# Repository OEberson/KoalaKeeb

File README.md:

# KoalaKeeb

In this repo, I am sharing with you my ideal split keyboard, The KoalaKeeb. It is heavily inspired by the [Ferris Sweep](https://github.com/davidphilipbarr/Sweep) and borrows its physical layout. What it adds is ten SK6812 MINI-E LEDs next to the MCU that will be used to display the current battery status or bluetooth profile and a cute koala logo. I will implement the LED functionality in [my ZMK fork](https://github.com/OEberson/zmkoala) soon.

Note that the current PCB version has some imperfections that I will improve on in a second revision.

[Link to my layout](https://github.com/OEberson/zmk-config)

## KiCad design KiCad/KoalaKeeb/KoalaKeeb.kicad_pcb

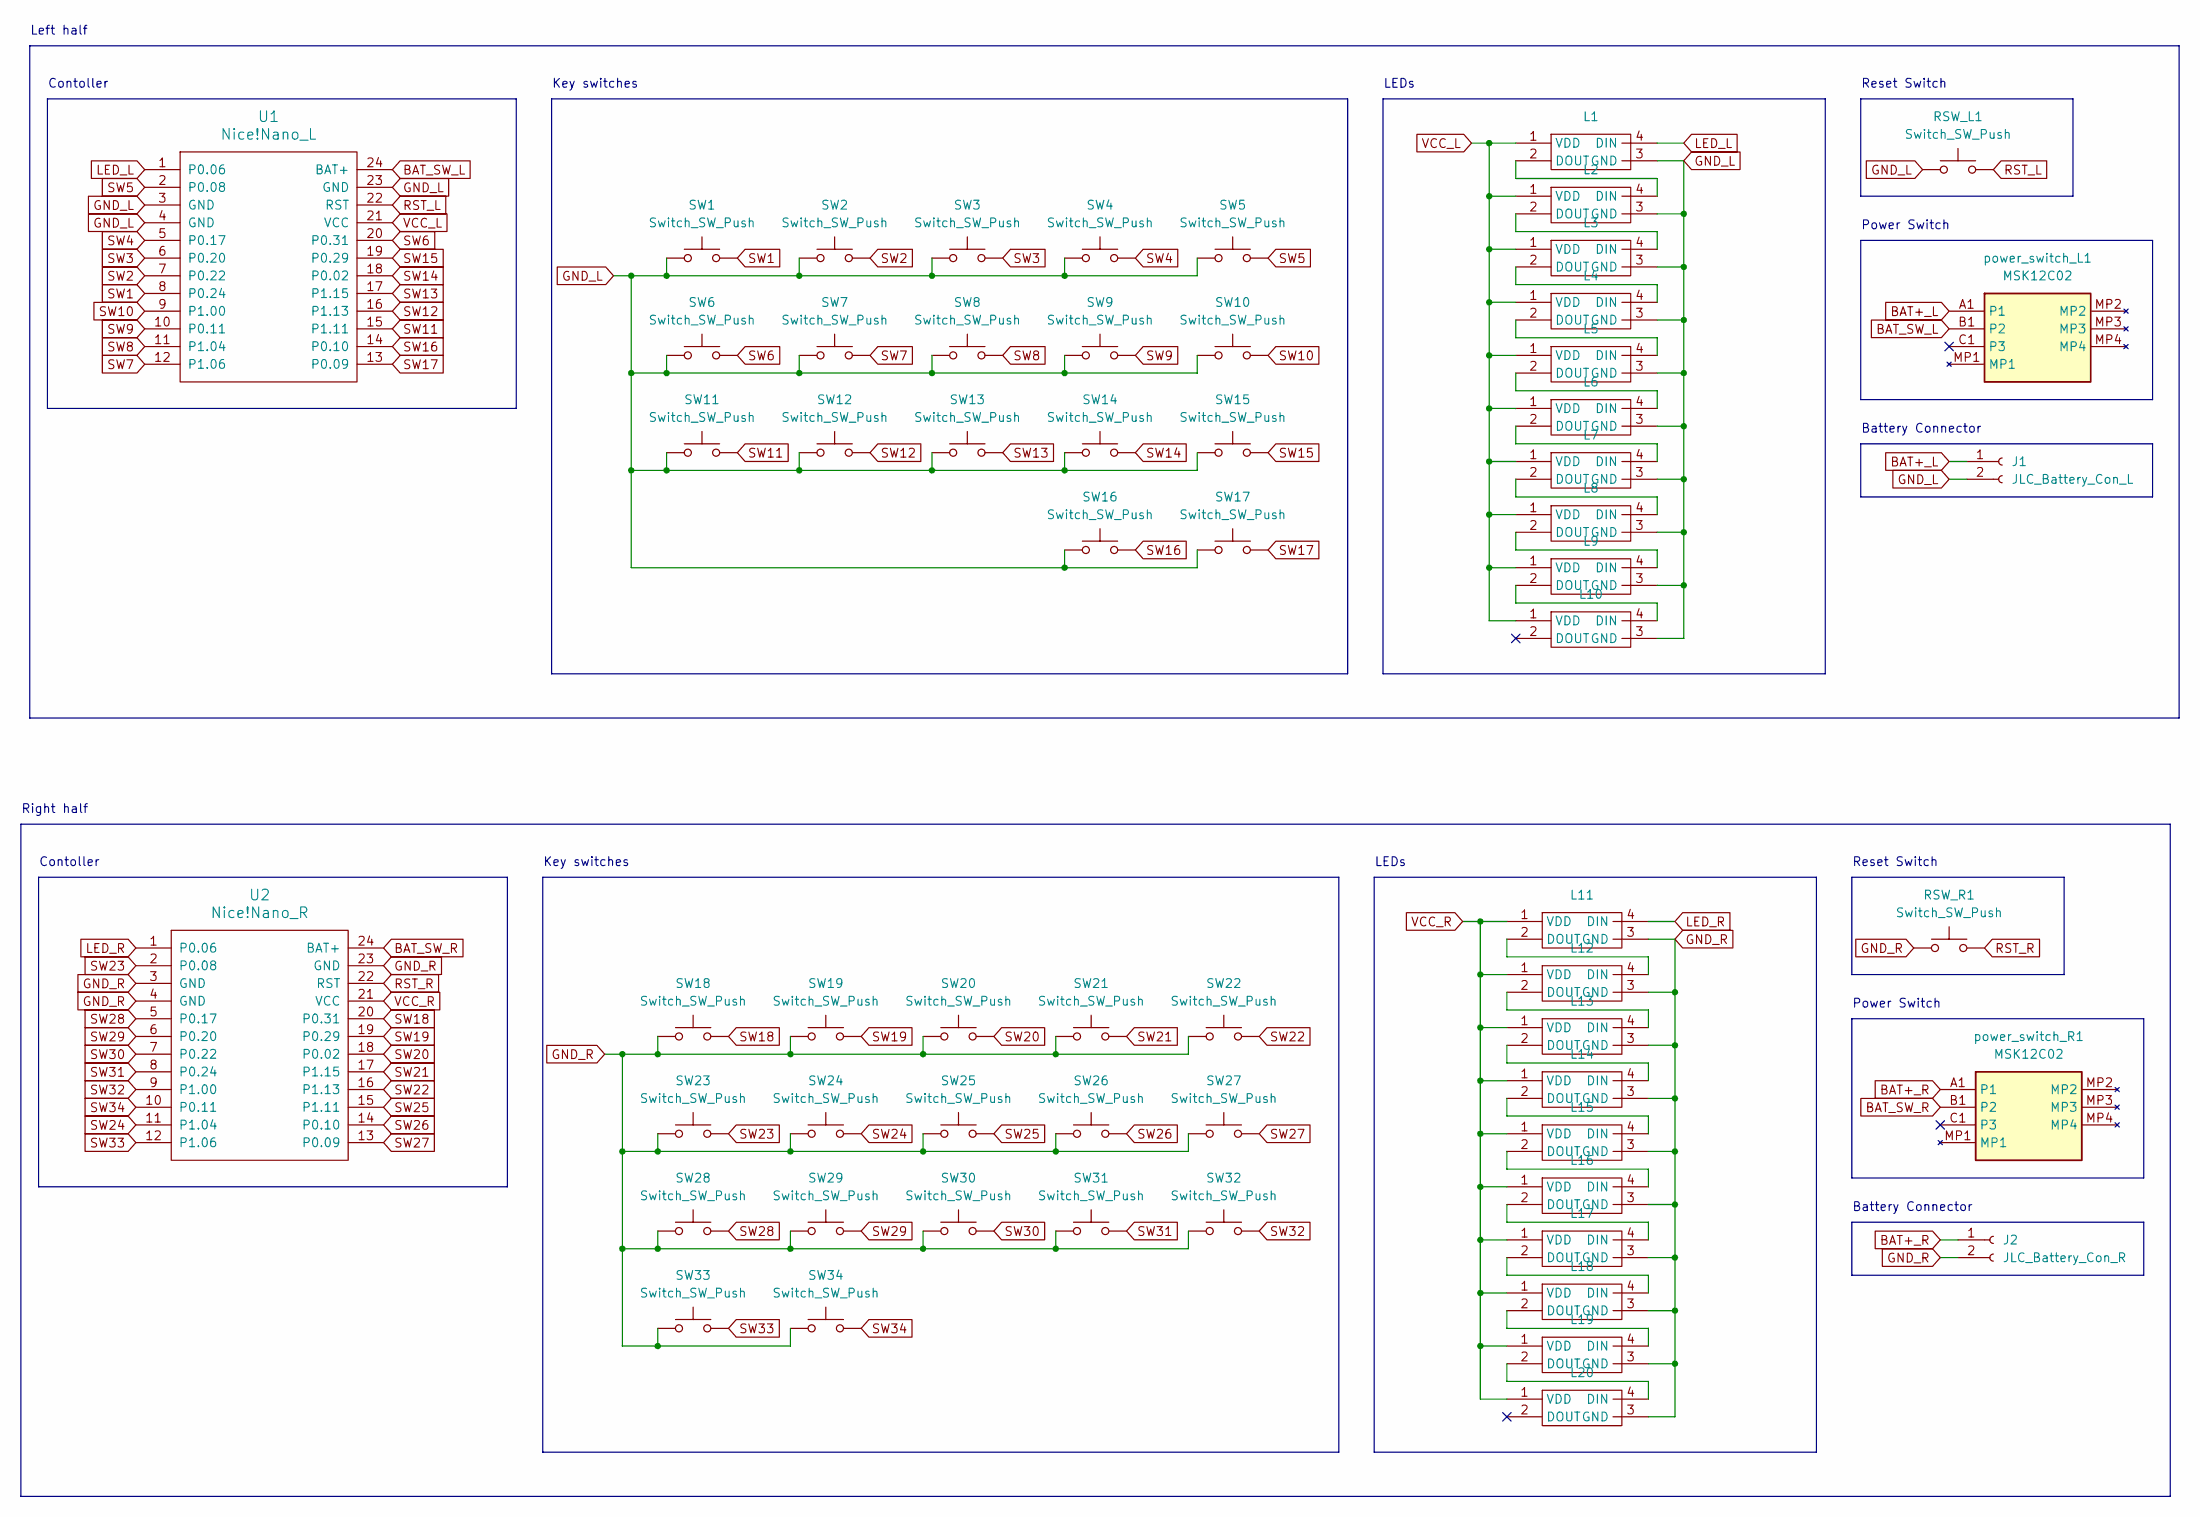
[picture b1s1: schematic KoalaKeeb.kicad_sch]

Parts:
J1: JLC_Battery_Con_L; JLC 2Pin
J2: JLC_Battery_Con_R; JLC 2Pin
L1, L2, L3, L4, L5, L6, L7, L8, L9, L10, L11, L12, L13, L14, L15, L16, L17, L18, L19, L20: SK6812-MINI-E
RSW_L1: Switch_SW_Push; TS-1136-4.3
RSW_R1: Switch_SW_Push; TS-1136-4.3
SW1, SW2, SW3, SW4, SW5, SW6, SW7, SW8, SW9, SW10, SW11, SW12, SW13, SW14, SW15, SW16, SW17, SW18, SW19, SW20, SW21, SW22, SW23, SW24, SW25, SW26, SW27, SW28, SW29, SW30, SW31, SW32, SW33, SW34: Switch_SW_Push; Kailh_socket_PG1350
U1: Nice!Nano_L; nice!nano
U2: Nice!Nano_R; nice!nano
power_switch_L1: MSK12C02; Manufacturer_Part_Number MSK12C02
power_switch_R1: MSK12C02; Manufacturer_Part_Number MSK12C02

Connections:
BAT+_L: J1.1, power_switch_L1.A1 (P1)
BAT+_R: J2.1, power_switch_R1.A1 (P1)
BAT_SW_L: U1.24 (BAT+), power_switch_L1.B1 (P2)
BAT_SW_R: U2.24 (BAT+), power_switch_R1.B1 (P2)
GND_L: J1.2, L1.3 (GND), L2.3 (GND), L3.3 (GND), L4.3 (GND), L5.3 (GND), L6.3 (GND), L7.3 (GND), L8.3 (GND), L9.3 (GND), L10.3 (GND), RSW_L1.1, SW1.1, SW2.1, SW3.1, SW4.1, SW5.1, SW6.1, SW7.1, SW8.1, SW9.1, SW10.1, SW11.1, SW12.1, SW13.1, SW14.1, SW15.1, SW16.1, SW17.1, U1.3 (GND), U1.4 (GND), U1.23 (GND)
GND_R: J2.2, L11.3 (GND), L12.3 (GND), L13.3 (GND), L14.3 (GND), L15.3 (GND), L16.3 (GND), L17.3 (GND), L18.3 (GND), L19.3 (GND), L20.3 (GND), RSW_R1.1, SW18.1, SW19.1, SW20.1, SW21.1, SW22.1, SW23.1, SW24.1, SW25.1, SW26.1, SW27.1, SW28.1, SW29.1, SW30.1, SW31.1, SW32.1, SW33.1, SW34.1, U2.3 (GND), U2.4 (GND), U2.23 (GND)
LED_L: L1.4 (DIN), U1.1 (P0.06)
LED_R: L11.4 (DIN), U2.1 (P0.06)
unnamed: L1.2 (DOUT), L2.4 (DIN)
unnamed: L2.2 (DOUT), L3.4 (DIN)
unnamed: L3.2 (DOUT), L4.4 (DIN)
unnamed: L4.2 (DOUT), L5.4 (DIN)
unnamed: L5.2 (DOUT), L6.4 (DIN)
unnamed: L6.2 (DOUT), L7.4 (DIN)
unnamed: L7.2 (DOUT), L8.4 (DIN)
unnamed: L8.2 (DOUT), L9.4 (DIN)
unnamed: L9.2 (DOUT), L10.4 (DIN)
unnamed: L11.2 (DOUT), L12.4 (DIN)
unnamed: L12.2 (DOUT), L13.4 (DIN)
unnamed: L13.2 (DOUT), L14.4 (DIN)
unnamed: L14.2 (DOUT), L15.4 (DIN)
unnamed: L15.2 (DOUT), L16.4 (DIN)
unnamed: L16.2 (DOUT), L17.4 (DIN)
unnamed: L17.2 (DOUT), L18.4 (DIN)
unnamed: L18.2 (DOUT), L19.4 (DIN)
unnamed: L19.2 (DOUT), L20.4 (DIN)
RST_L: RSW_L1.2, U1.22 (RST)
RST_R: RSW_R1.2, U2.22 (RST)
SW1: SW1.2, U1.8 (P0.24)
SW2: SW2.2, U1.7 (P0.22)
SW3: SW3.2, U1.6 (P0.20)
SW4: SW4.2, U1.5 (P0.17)
SW5: SW5.2, U1.2 (P0.08)
SW6: SW6.2, U1.20 (P0.31)
SW7: SW7.2, U1.12 (P1.06)
SW8: SW8.2, U1.11 (P1.04)
SW9: SW9.2, U1.10 (P0.11)
SW10: SW10.2, U1.9 (P1.00)
SW11: SW11.2, U1.15 (P1.11)
SW12: SW12.2, U1.16 (P1.13)
SW13: SW13.2, U1.17 (P1.15)
SW14: SW14.2, U1.18 (P0.02)
SW15: SW15.2, U1.19 (P0.29)
SW16: SW16.2, U1.14 (P0.10)
SW17: SW17.2, U1.13 (P0.09)
SW18: SW18.2, U2.20 (P0.31)
SW19: SW19.2, U2.19 (P0.29)
SW20: SW20.2, U2.18 (P0.02)
SW21: SW21.2, U2.17 (P1.15)
SW22: SW22.2, U2.16 (P1.13)
SW23: SW23.2, U2.2 (P0.08)
SW24: SW24.2, U2.11 (P1.04)
SW25: SW25.2, U2.15 (P1.11)
SW26: SW26.2, U2.14 (P0.10)
SW27: SW27.2, U2.13 (P0.09)
SW28: SW28.2, U2.5 (P0.17)
SW29: SW29.2, U2.6 (P0.20)
SW30: SW30.2, U2.7 (P0.22)
SW31: SW31.2, U2.8 (P0.24)
SW32: SW32.2, U2.9 (P1.00)
SW33: SW33.2, U2.12 (P1.06)
SW34: SW34.2, U2.10 (P0.11)
VCC_L: L1.1 (VDD), L2.1 (VDD), L3.1 (VDD), L4.1 (VDD), L5.1 (VDD), L6.1 (VDD), L7.1 (VDD), L8.1 (VDD), L9.1 (VDD), L10.1 (VDD), U1.21 (VCC)
VCC_R: L11.1 (VDD), L12.1 (VDD), L13.1 (VDD), L14.1 (VDD), L15.1 (VDD), L16.1 (VDD), L17.1 (VDD), L18.1 (VDD), L19.1 (VDD), L20.1 (VDD), U2.21 (VCC)

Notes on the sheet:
Contoller
Key switches
Reset Switch
Power Switch
LEDs
Left half
Battery Connector
Right half

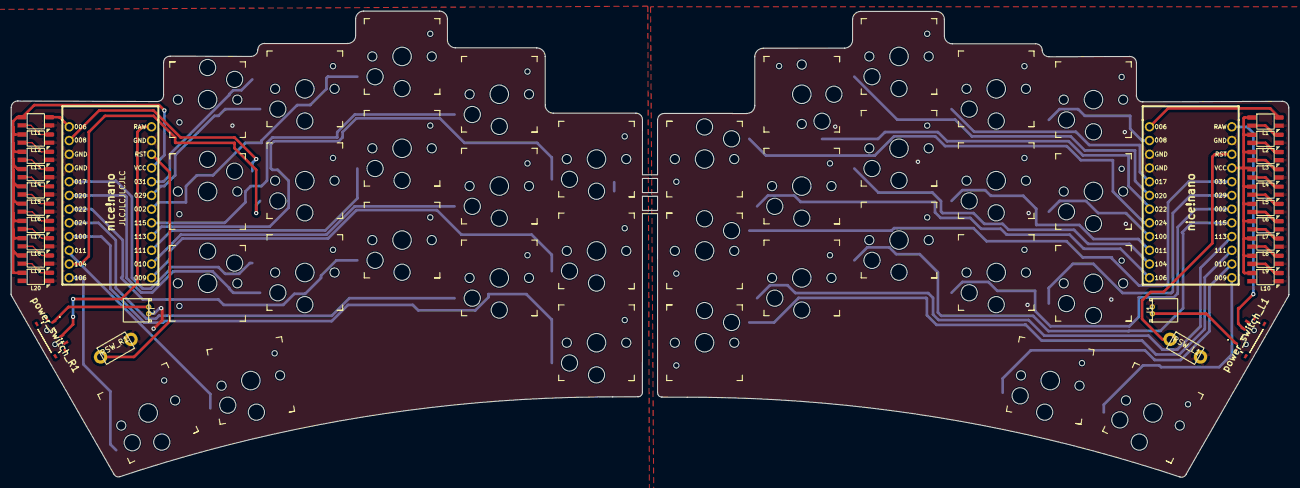
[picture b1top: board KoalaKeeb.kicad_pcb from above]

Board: 2 copper layers, 236.6 x 86.3 mm, 62 parts (0 on the bottom side), 64 nets.

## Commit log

2023-08-19 remove transistor circuit
2023-08-19 add readme
2023-08-19 remove diodes
2023-08-19 add right half
2023-08-19 add and assing most footprints
2023-08-20 add remaining footprints and create PCB
2023-08-20 add new footprints to git
2023-08-20 place all parts for left side
2023-08-20 place all components on PCB
2023-08-20 routing and outlines done
2023-08-20 connect PCB halves
2023-08-20 add text field for JLC serial number
2023-08-23 update routing for right half LEDs
2023-08-23 add .gitignore file
2023-08-23 add backup folder to .gitignore
2023-08-29 add logo and create gerber files
2023-09-20 update readme and add picture
2024-06-21 add link to layout repo
2024-09-20 add step file
2024-09-20 fix LED footprint
2024-09-20 add v0.2 as extra files
2024-09-20 add v0.2
2024-10-04 split v0.2 into left and right
2024-11-22 add v1
2024-11-22 remove ltspice folder - no longer needed
